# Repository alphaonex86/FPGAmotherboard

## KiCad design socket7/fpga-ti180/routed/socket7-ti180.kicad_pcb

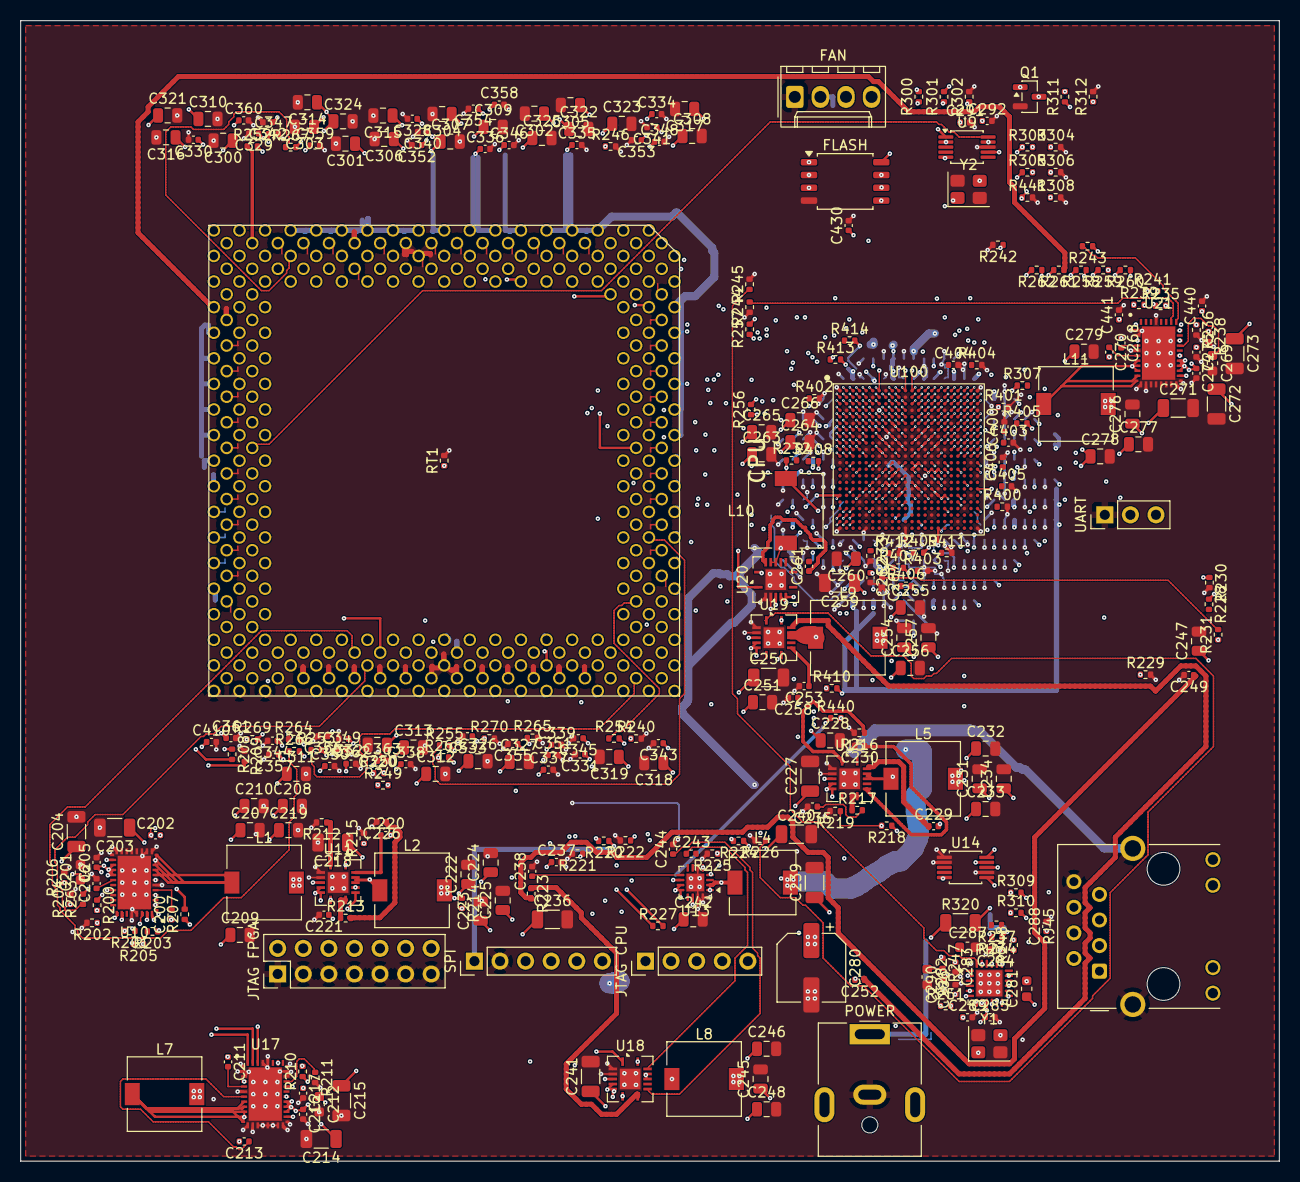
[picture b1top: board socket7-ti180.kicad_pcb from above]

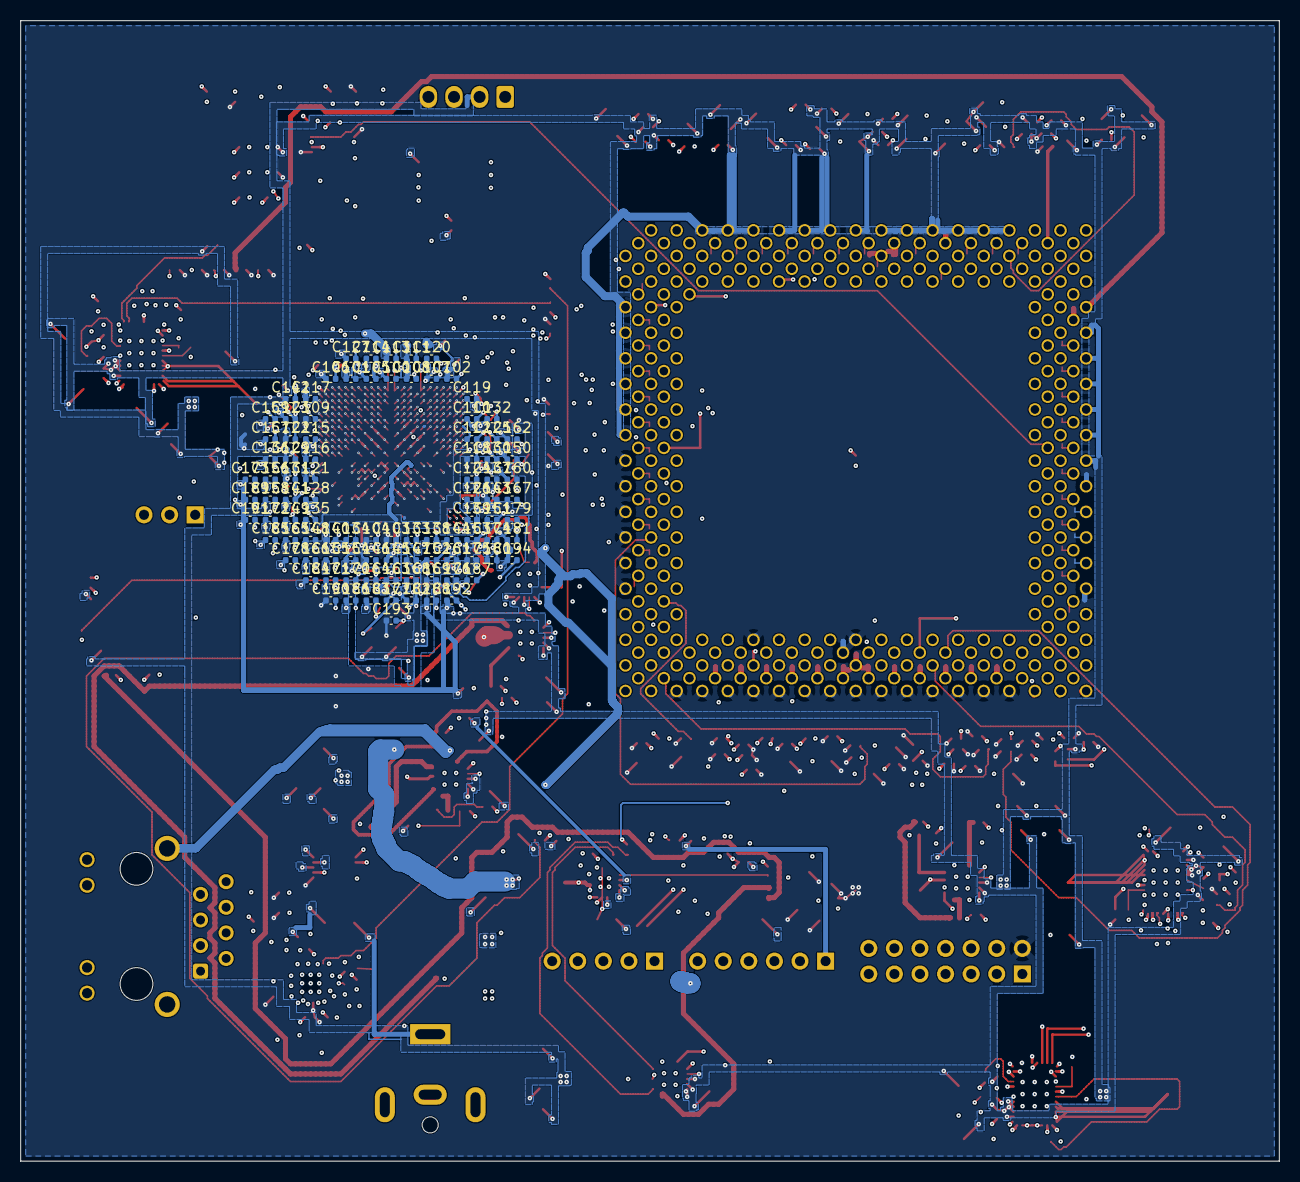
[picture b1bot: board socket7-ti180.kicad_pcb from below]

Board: 6 copper layers, 124.9 x 113.2 mm, 398 parts (95 on the bottom side), 290 nets.

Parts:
C100, C101, C102, C103, C104, C105, C106, C107, C108, C109, C110, C111, C112, C113, C114, C115, C116, C117, C118, C119, C120, C121, C122, C123, C124, C125, C126, C127, C128, C129, C130, C131, C132, C133, C134, C135, C136, C137, C138, C139, C140, C141, C142, C143, C144, C145, C146, C147, C148, C149, C150, C151, C152, C153, C154, C155, C156, C157, C158, C159, C160, C161, C162, C163, C164, C165, C166, C167, C168, C169, C170, C171, C172, C173, C174, C175, C176, C177, C178, C179, C180, C181, C182, C183, C184, C185, C186, C187, C188, C189, C190, C191, C192, C193, C194: 470nF; C_0402_1005Metric
C200, C211, C268: 1uF 16V X6S; C_0402_1005Metric
C201, C212, C269: 4.7uF 16V X5R; C_0603_1608Metric
C202, C213, C270: 100nF 16V X5R; C_0402_1005Metric
C203, C204, C214, C215, C218, C227, C236, C239, C240, C241, C250, C259, C271, C272, C273: 22uF 25V X5R; C_1206_3216Metric
C205, C216, C221, C230, C244, C253, C262, C274, C403, C404, C405, C406: 10nF 50V X7R; C_0402_1005Metric
C206, C217, C275: 1uF 25V X5R; C_0402_1005Metric
C207, C208, C209, C210, C222, C223, C224, C225, C245, C246, C247, C248, C254, C255, C256, C257, C263, C264, C265, C266, C276, C277, C278, C279: 47uF 6.3V X5R; C_0805_2012Metric
C219, C228, C242, C251, C260: 4.7uF 25V X7R; C_0805_2012Metric
C220, C229, C237, C243, C252, C261, C283, C284, C285, C288, C410, C430: 100nF 16V X7R; C_0402_1005Metric
C226, C235, C249, C258, C267: 8.2nF 50V X7R; C_0402_1005Metric
C231, C232, C233, C234: 47uF 10V X5R; C_0805_2012Metric
C238: 3.3nF 50V X7R; C_0402_1005Metric
C280: 100uF 25V; CP_Elec_6.3x7.7
C281: 600R@100MHz bead; L_0603_1608Metric
C282: 10uF 10V X5R; C_0603_1608Metric
C286: 470pF 50V C0G; C_0402_1005Metric
C287: 1uF 16V X7R; C_0603_1608Metric
C289, C290: 15pF 50V C0G; C_0402_1005Metric
C291, C292: 4pF 50V C0G; C_0402_1005Metric
C300, C301, C302, C303, C304, C305, C306, C307, C308, C309, C310, C311, C312, C313, C314, C315, C316, C317, C318, C319, C320, C321, C322, C323, C324, C325, C326, C327: 22uF; C_0805_2012Metric
C328, C329, C330, C331, C332, C333, C334, C335, C336, C337, C338, C339, C340, C341, C342, C343, C344, C345, C346, C347, C348, C349, C350, C351, C352, C353, C354, C355, C356, C357, C358, C359, C360, C361, C362, C363: 100nF; C_0402_1005Metric
C400: 1nF 50V C0G; C_0402_1005Metric
C440: 22nF 50V X7R; C_0402_1005Metric
C441: 1uF 16V X7R; C_0402_1005Metric
J1: HR911105A; RJ45_Hanrun_HR911105A_Horizontal
J2: SPI ISP; PinHeader_1x06_P2.54mm_Vertical
J3: PJ-063AH 12V; BarrelJack_CUI_PJ-063AH_Horizontal
J4: UART; PinHeader_1x03_P2.54mm_Vertical
J5: FPGA JTAG; PinHeader_2x07_P2.54mm_Vertical
J6: CPU JTAG; PinHeader_1x05_P2.54mm_Vertical
J7: fan 4-pin 1GND 2+12V 3TACH 4PWM; Molex_KK-254_AE-6410-04A_1x04_P2.54mm_Vertical
L1: VCC2 out; L_7.3x7.3_H4.5
L2: 3V3 out; L_7.3x7.3_H4.5
L4: 1V8 out; L_6.3x6.3_H3
L5: 5V out; L_7.3x7.3_H4.5
L7: VCC2 ph2 out; L_7.3x7.3_H4.5
L8: 0V95 out; L_7.3x7.3_H4.5
L9: 0V85 out; L_7.3x7.3_H4.5
L10: 1V1 out; L_7.3x7.3_H4.5
L11: 0V6 out; L_7.3x7.3_H4.5
Q1: BSS138; SOT-23
R200, R210, R234: 10R 1%; R_0402_1005Metric
R201, R202, R205, R239, R240: 21.5k 1%; R_0402_1005Metric
R203: 110k 1%; R_0402_1005Metric
R204: 56.2k 1%; R_0402_1005Metric
R206, R214, R235: 31.6k 1%; R_0402_1005Metric
R207, R215, R219, R221, R225, R229, R233, R246, R265, R270, R301, R302, R303, R305, R309, R310, R311, R400, R401, R402, R403, R404, R406, R407, R408, R409, R410, R411, R412, R413, R414, R440: 10k 1%; R_0402_1005Metric
R208, R209, R243, R244: 0R; R_0402_1005Metric
R211: 17.8k 1%; R_0402_1005Metric
R212, R216, R222, R226, R230: 100k 1%; R_0402_1005Metric
R213, R217, R223, R227, R231, R300: 1.69k 1%; R_0402_1005Metric
R218: 52.3k 1%; R_0402_1005Metric
R220: 12.4k 1%; R_0402_1005Metric
R224: 1.87k 1%; R_0402_1005Metric
R228: 619R 1%; R_0402_1005Metric
R232: 3.74k 1%; R_0402_1005Metric
R236: 6.81k 1%; R_0402_1005Metric
R237: 90.9k 1%; R_0402_1005Metric
R238: 46.4k 1%; R_0402_1005Metric
R241: 1.54k 1%; R_0402_1005Metric
R242: 5.62k 1%; R_0402_1005Metric
R245: 12.1k 1%; R_0402_1005Metric
R247, R248, R249, R250: 49.9 1%; R_0402_1005Metric
R251: 500R 1%; R_0402_1005Metric
R252, R261, R262, R264, R269: 8.2k 1%; R_0402_1005Metric
R253, R254, R255, R256, R257, R258, R259, R260, R263, R266, R267, R268: 4.7k 1%; R_0402_1005Metric
R304, R306, R312: 4.02k 1%; R_0402_1005Metric
R307: 30.9k 1%; R_0402_1005Metric
R308: 2.49k 1%; R_0402_1005Metric
R320: 10mR 1% 1W; R_1206_3216Metric
R405: 240R 1%; R_0402_1005Metric
R441: 22k 1%; R_0402_1005Metric
RT1: 10k NTC 1% B3380; R_0402_1005Metric
U7: LAN8720A-CP-TR; QFN-24-1EP_4x4mm_P0.5mm_EP2.6x2.6mm
U8: W25Q128JWSIQ; SOIC-8_5.3x5.3mm_P1.27mm
U9: SI5351A-B-GTR; MSOP-10_3x3mm_P0.5mm
U10: TPS546B24ARVFR VCC2; Texas_RVF0040A_LQFN-CLIP-40_5x7mm_P0.5mm
U11: TPS54620RGYR 3V3; Texas_S-PVQFN-N14
U13: TPS62130RGTR 1V8; QFN-16-1EP_3x3mm_P0.5mm_EP1.75x1.75mm
U14: INA226AIDGSR; MSOP-10_3x3mm_P0.5mm
U15: TPS54620RGYR 5V; Texas_S-PVQFN-N14
U17: TPS546B24ARVFR VCC2 ph2; Texas_RVF0040A_LQFN-CLIP-40_5x7mm_P0.5mm
U18: TPS54620RGYR 0V95; Texas_S-PVQFN-N14
U19: TPS54620RGYR 0V85; Texas_S-PVQFN-N14
U20: TPS54620RGYR 1V1; Texas_S-PVQFN-N14
U21: TPS546B24ARVFR 0V6; Texas_RVF0040A_LQFN-CLIP-40_5x7mm_P0.5mm
U100: Ti180J484D1C4
XU1: Socket 7 ZIF 321p; Socket7_P55C_296
Y1, Y2: 25MHz; Crystal_SMD_3225-4Pin_3.2x2.5mm

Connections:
0v62_gsense: R244.2, U21.34
0v62_sense: R243.2, U21.33
+0V62: C153.1, C155.1, C156.1, C157.1, C161.1, C163.1, C164.1, C168.1, C172.1, C178.1, C184.1, C185.1, C186.1, C276.1, C277.1, C278.1, C279.1, L11.2, R243.1, R405.2, U100.N8, U100.N10, U100.N14, U100.N15, U100.N16, U100.P9, U100.P11, U100.P13, U100.R16, U100.T15, U100.U14, U100.U16, U100.U17
+0V85: C139.1, C140.1, C141.1, C145.1, C146.1, C147.1, C148.1, C152.1, C154.1, C162.1, C166.1, C254.1, C255.1, C256.1, C257.1, L9.2, R228.1, U100.L10, U100.L12, U100.L14, U100.M9, U100.M11, U100.M12, U100.M13, U100.M15, U100.N9, U100.N12, U100.P16
+0V95: C114.1, C115.1, C116.1, C119.1, C120.1, C121.1, C122.1, C124.1, C125.1, C126.1, C127.1, C128.1, C129.1, C132.1, C133.1, C134.1, C135.1, C137.1, C138.1, C142.1, C144.1, C151.1, C158.1, C180.1, C245.1, C246.1, C247.1, C248.1, L8.2, R224.1, U100.G8, U100.G12, U100.G14, U100.G17, U100.H7, U100.H9, U100.H11, U100.H13, U100.H15, U100.J8, U100.J10, U100.J12, U100.J14, U100.J16, U100.K7, U100.K9, U100.K11, U100.K13, U100.K15, U100.L8, U100.L16, U100.M7, U100.N17, U100.T7
+1V1: C165.1, C167.1, C169.1, C170.1, C171.1, C174.1, C175.1, C176.1, C177.1, C182.1, C263.1, C264.1, C265.1, C266.1, L10.2, R232.1, U100.P7, U100.P15, U100.R8, U100.R9, U100.R10, U100.R12, U100.R14, U100.T11, U100.T13, U100.U10
+1V8: C100.1, C101.1, C102.1, C105.1, C106.1, C107.1, C108.1, C110.1, C111.1, C112.1, C113.1, C117.1, C123.1, C130.1, C131.1, C136.1, C143.1, C149.1, C150.1, C159.1, C160.1, C173.1, C179.1, C181.1, C183.1, C188.1, C189.1, C191.1, C192.1, C194.1, C239.1, C240.1, C430.1, J2.1, L4.2, R220.1, R406.2, R407.2, R408.2, R409.2, R410.2, R413.2, R414.2, U8.8, U13.14, U100.A3, U100.A13, U100.A19, U100.C4, U100.C9, U100.C14, U100.C19, U100.E5, U100.F9, U100.G1, U100.G10, U100.G21, U100.H17, U100.J2, U100.J22, U100.K20, U100.L3, U100.M6, U100.M17, U100.N4, U100.N19, U100.R20, U100.T3, U100.U1, U100.U7, U100.U12, U100.V19, U100.W6, U100.W22, U100.Y2
+3V3: C103.1, C104.1, C109.1, C118.1, C190.1, C193.1, C222.1, C223.1, C224.1, C225.1, C281.1, C285.1, C311.1, C312.1, C313.1, C318.1, C319.1, C320.1, C326.1, C327.1, C331.1, C332.1, C333.1, C337.1, C338.1, C339.1, C343.1, C344.1, C345.1, C349.1, C350.1, C351.1, C355.1, C356.1, C357.1, C361.1, C362.1, C363.1, C410.1, J5.2, L2.2, R207.1, R214.1, R252.2, R253.2, R254.2, R255.2, R256.2, R257.2, R258.2, R259.2, R260.2, R261.2, R262.2, R263.2, R264.2, R266.2, R267.2, R268.2, R269.2, R301.2, R305.1, R309.2, R310.2, R311.1, U7.9, U9.1, U9.7, U14.6, U100.AA13, U100.AB16, U100.E20, U100.G7, U100.W17, U100.Y10, XU1.A19 (VCC3), XU1.A21 (VCC3), XU1.A23 (VCC3), XU1.A25 (VCC3), XU1.A27 (VCC3), XU1.A29 (VCC3), XU1.AA37 (VCC3), XU1.AC37 (VCC3), XU1.AE37 (VCC3), XU1.AG37 (VCC3), XU1.AN21 (VCC3), XU1.AN23 (VCC3), XU1.AN25 (VCC3), XU1.AN27 (VCC3), XU1.AN29 (VCC3), XU1.E37 (VCC3), XU1.G37 (VCC3), XU1.J37 (VCC3), XU1.L33 (VCC3), XU1.L37 (VCC3), XU1.N37 (VCC3), XU1.Q37 (VCC3), XU1.S37 (VCC3), XU1.T34 (VCC3), XU1.U33 (VCC3), XU1.U37 (VCC3), XU1.W37 (VCC3), XU1.Y37 (VCC3)
+5V: C231.1, C232.1, C233.1, C234.1, C236.1, C237.1, L5.2, R218.1, R440.1, U13.10, U13.11, U13.12
+12V: C203.1, C204.1, C205.1, C214.1, C215.1, C216.1, C218.1, C219.1, C227.1, C228.1, C241.1, C242.1, C250.1, C251.1, C259.1, C260.1, C271.1, C272.1, C273.1, C274.1, C280.1, J7.2, R200.1, R210.1, R234.1, R307.1, R320.2, U10.22, U10.23, U10.24, U10.25, U11.4, U11.5, U11.6, U14.8, U14.9, U15.4, U15.5, U15.6, U17.22, U17.23, U17.24, U17.25, U18.4, U18.5, U18.6, U19.4, U19.5, U19.6, U20.4, U20.5, U20.6, U21.22, U21.23, U21.24, U21.25
+12V_IN: J3.1, R320.1, U14.10
GND: C100.2, C101.2, C102.2, C103.2, C104.2, C105.2, C106.2, C107.2, C108.2, C109.2, C110.2, C111.2, C112.2, C113.2, C114.2, C115.2, C116.2, C117.2, C118.2, C119.2, C120.2, C121.2, C122.2, C123.2, C124.2, C125.2, C126.2, C127.2, C128.2, C129.2, C130.2, C131.2, C132.2, C133.2, C134.2, C135.2, C136.2, C137.2, C138.2, C139.2, C140.2, C141.2, C142.2, C143.2, C144.2, C145.2, C146.2, C147.2, C148.2, C149.2, C150.2, C151.2, C152.2, C153.2, C154.2, C155.2, C156.2, C157.2, C158.2, C159.2, C160.2, C161.2, C162.2, C163.2, C164.2, C165.2, C166.2, C167.2, C168.2, C169.2, C170.2, C171.2, C172.2, C173.2, C174.2, C175.2, C176.2, C177.2, C178.2, C179.2, C180.2, C181.2, C182.2, C183.2, C184.2, C185.2, C186.2, C187.1, C187.2, C188.2, C189.2, C190.2, C191.2, C192.2, C193.2, C194.2, C201.2, C203.2, C204.2, C205.2, C206.2, C207.2, C208.2, C209.2, C210.2, C212.2, C214.2, C215.2, C216.2, C217.2, C218.2, C219.2, C221.2, C222.2, C223.2, C224.2, C225.2, C226.2, C227.2, C228.2, C230.2, C231.2, C232.2, C233.2, C234.2, C235.2, C236.2, C237.2, C238.2, C239.2, C240.2, C241.2, C242.2, C244.2, C245.2, C246.2, C247.2, C248.2, C249.2, C250.2, C251.2, C253.2, C254.2, C255.2, C256.2, C257.2, C258.2, C259.2, C260.2, C262.2, C263.2, C264.2, C265.2, C266.2, C267.2, C269.2, C271.2, C272.2, C273.2, C274.2, C275.2, C276.2, C277.2, C278.2, C279.2, C280.2, C282.2, C283.2, C284.2, C285.2, C286.2, C287.2, C288.2, C289.2, C290.2, C291.2, C292.2, C300.2, C301.2, C302.2, C303.2, C304.2, C305.2, C306.2, C307.2, C308.2, C309.2, C310.2, C311.2, C312.2, C313.2, C314.2, C315.2, C316.2, C317.2, C318.2, C319.2, C320.2, C321.2, C322.2, C323.2, C324.2, C325.2, C326.2, C327.2, C328.2, C329.2, C330.2, C331.2, C332.2, C333.2, C334.2, C335.2, C336.2, C337.2, C338.2, C339.2, C340.2, C341.2, C342.2, C343.2, C344.2, C345.2, C346.2, C347.2, C348.2, C349.2, C350.2, C351.2, C352.2, C353.2, C354.2, C355.2, C356.2, C357.2, C358.2, C359.2, C360.2, C361.2, C362.2, C363.2, C400.2, C403.2, C404.2, C405.2, C406.2, C410.2, C430.2, C440.2, C441.2, J1.8, J1.SH, J2.2, J3.2, J4.1, J5.1, J5.3, J5.5, J5.7, J5.9, J5.11, J5.13, J7.1, Q1.2, R202.2, R204.2, R206.2, R209.1, R211.2, R212.2, R215.2, R216.2, R219.2, R221.2, R222.2, R225.2, R226.2, R229.2, R230.2, R233.2, R236.2, R238.2, R240.2, R242.2, R244.1, R245.2, R246.2, R265.2, R270.2, R302.2, R304.2, R306.2, R308.2, R312.2, R400.2, R401.2, R402.2, R403.2, R404.2, R411.2, R412.2, R441.2, RT1.2, U7.25, U8.4, U9.8, U10.6, U10.13, U10.14, U10.15, U10.16, U10.17, U10.18, U10.19, U10.20, U10.21, U10.36, U10.37, U10.41, U11.2, U11.3, U11.15, U13.6, U13.15, U13.16, U13.17, U14.1, U14.2, U14.7, U15.2, U15.3, U15.15, U17.1, U17.2, U17.3, U17.6, U17.13, U17.14, U17.15, U17.16, U17.17, U17.18, U17.19, U17.20, U17.21, U17.30, U17.31, U17.32, U17.36, U17.37, U17.41, U18.2, U18.3, U18.15, U19.2, U19.3, U19.15, U20.2, U20.3, U20.15, U21.2, U21.3, U21.6, U21.13, U21.14, U21.15, U21.16, U21.17, U21.18, U21.19, U21.20, U21.21, U21.37, U21.41, U100.A1, U100.A8, U100.A22, U100.AA8, U100.AA19, U100.AB1, U100.AB5, U100.AB11, U100.AB22, U100.B6, U100.B11, U100.B16, U100.D2, U100.D7, U100.D12, U100.D17, U100.D22, U100.E15, U100.F3, U100.F18, U100.G9, U100.G11, U100.G13, U100.G15, U100.H4, U100.H8, U100.H10, U100.H12, U100.H14, U100.H16, U100.H19, U100.J7, U100.J9, U100.J11, U100.J13, U100.J15, U100.K5, U100.K8, U100.K10, U100.K12, U100.K14, U100.K16, U100.K17, U100.L7, U100.L9, U100.L11, U100.L13, U100.L15, U100.M1, U100.M8, U100.M10, U100.M14, U100.M16, U100.M21, U100.N7, U100.N11, U100.N13, U100.P2, U100.P8, U100.P10, U100.P12, U100.P14, U100.P22, U100.R7, U100.R11, U100.R13, U100.R15, U100.R17, U100.T8, U100.T10, U100.T12, U100.T14, U100.T16, U100.U5, U100.U13, U100.U15, U100.U21, U100.V4, U100.V9, U100.W7, U100.W20, U100.Y5, U100.Y15, XU1.AB02 (VSS), XU1.AB04 (HOLD), XU1.AB36 (VSS), XU1.AD02 (VSS), XU1.AD36 (VSS), XU1.AF02 (VSS), XU1.AF36 (VSS), XU1.AH02 (VSS), XU1.AJ37 (VSS), XU1.AL37 (VSS), XU1.AM08 (VSS), XU1.AM10 (VSS), XU1.AM12 (VSS), XU1.AM14 (VSS), XU1.AM16 (VSS), XU1.AM18 (VSS), XU1.AM20 (VSS), XU1.AM22 (VSS), XU1.AM24 (VSS), XU1.AM26 (VSS), XU1.AM28 (VSS), XU1.AM30 (VSS), XU1.AN37 (VSS), XU1.B06 (VSS), XU1.B08 (VSS), XU1.B10 (VSS), XU1.B12 (VSS), XU1.B14 (VSS), XU1.B16 (VSS), XU1.B18 (VSS), XU1.B20 (VSS), XU1.B22 (VSS), XU1.B24 (VSS), XU1.B26 (VSS), XU1.B28 (VSS), XU1.H02 (VSS), XU1.H36 (VSS), XU1.K02 (VSS), XU1.K36 (VSS), XU1.M02 (VSS), XU1.M36 (VSS), XU1.P02 (VSS), XU1.P36 (VSS), XU1.R02 (VSS), XU1.R36 (VSS), XU1.T02 (VSS), XU1.T36 (VSS), XU1.U35 (VSS), XU1.V02 (VSS), XU1.V36 (VSS), XU1.W03 (EWBE#), XU1.X02 (VSS), XU1.X36 (VSS), XU1.Z02 (VSS), XU1.Z36 (VSS), Y1.2, Y1.4, Y2.2, Y2.4
VCC2: C207.1, C208.1, C209.1, C210.1, C300.1, C301.1, C302.1, C303.1, C304.1, C305.1, C306.1, C307.1, C308.1, C309.1, C310.1, C314.1, C315.1, C316.1, C317.1, C321.1, C322.1, C323.1, C324.1, C325.1, C328.1, C329.1, C330.1, C334.1, C335.1, C336.1, C340.1, C341.1, C342.1, C346.1, C347.1, C348.1, C352.1, C353.1, C354.1, C358.1, C359.1, C360.1, L1.2, L7.2, R208.1, R303.1, XU1.A07 (VCC2), XU1.A09 (VCC2), XU1.A11 (VCC2), XU1.A13 (VCC2), XU1.A15 (VCC2), XU1.A17 (VCC2), XU1.AA01 (VCC2), XU1.AC01 (VCC2), XU1.AE01 (VCC2), XU1.AG01 (VCC2), XU1.AN09 (VCC2), XU1.AN11 (VCC2), XU1.AN13 (VCC2), XU1.AN15 (VCC2), XU1.AN17 (VCC2), XU1.AN19 (VCC2), XU1.G01 (VCC2), XU1.J01 (VCC2), XU1.L01 (VCC2), XU1.N01 (VCC2), XU1.Q01 (VCC2), XU1.S01 (VCC2), XU1.U01 (VCC2), XU1.W01 (VCC2), XU1.Y01 (VCC2)
cbsel0: R411.1, U100.R6
cbsel1: R412.1, U100.T6
cck: J2.4, U8.6, U100.AA3
cdi0: J2.6, U8.5, U100.W2
cdi1: J2.5, U8.2, U100.W3
cdi2: R413.1, U8.3, U100.AA1
cdi3: R414.1, U8.7, U100.Y1
cdone: R407.1, U100.U8
cpu_a20m_n: U100.E3, XU1.AK08 (A20M#)
cpu_a[3]: U100.J4, XU1.AL35 (A3)
cpu_a[4]: U100.H5, XU1.AM34 (A4)
cpu_a[5]: U100.K1, XU1.AK32 (A5)
cpu_a[6]: U100.C18, XU1.AN33 (A6)
cpu_a[7]: U100.J3, XU1.AL33 (A7)
cpu_a[8]: U100.B15, XU1.AM32 (A8)
cpu_a[9]: U100.E9, XU1.AK30 (A9)
cpu_a[10]: U100.J1, XU1.AN31 (A10)
cpu_a[11]: U100.G4, XU1.AL31 (A11)
cpu_a[12]: U100.G6, XU1.AL29 (A12)
cpu_a[13]: U100.E11, XU1.AK28 (A13)
cpu_a[14]: U100.E7, XU1.AL27 (A14)
cpu_a[15]: U100.H1, XU1.AK26 (A15)
cpu_a[16]: U100.D13, XU1.AL25 (A16)
cpu_a[17]: U100.G3, XU1.AK24 (A17)
cpu_a[18]: U100.F6, XU1.AL23 (A18)
cpu_a[19]: U100.F7, XU1.AK22 (A19)
cpu_a[20]: U100.F1, XU1.AL21 (A20)
cpu_a[21]: U100.D19, XU1.AF34 (A21)
cpu_a[22]: U100.D16, XU1.AH36 (A22)
cpu_a[23]: U100.J5, XU1.AE33 (A23)
cpu_a[24]: U100.F10, XU1.AG35 (A24)
cpu_a[25]: U100.K3, XU1.AJ35 (A25)
cpu_a[26]: U100.F11, XU1.AH34 (A26)
cpu_a[27]: U100.F13, XU1.AG33 (A27)
cpu_a[28]: U100.D15, XU1.AK36 (A28)
cpu_a[29]: U100.K2, XU1.AK34 (A29)
cpu_a[30]: U100.L1, XU1.AM36 (A30)
cpu_a[31]: U100.F12, XU1.AJ33 (A31)
cpu_ads_n: U100.E2, XU1.AJ05 (ADS#)
cpu_ahold: U100.C5, XU1.V04 (AHOLD)
cpu_ap: R252.1, XU1.AK02 (AP)
cpu_be[0]: U100.C3, XU1.AL09 (BE0#)
cpu_be[1]: U100.D3, XU1.AK10 (BE1#)
cpu_be[2]: U100.E8, XU1.AL11 (BE2#)
cpu_be[3]: U100.D5, XU1.AK12 (BE3#)
cpu_be[4]: U100.F4, XU1.AL13 (BE4#)
cpu_be[5]: U100.D11, XU1.AK14 (BE5#)
cpu_be[6]: U100.F2, XU1.AL15 (BE6#)
cpu_be[7]: U100.D10, XU1.AK16 (BE7#)
cpu_bf[0]: U100.G2, XU1.Y33 ([BF0])
cpu_bf[1]: U100.C16, XU1.X34 ([BF1])
cpu_boff_n: U100.B2, XU1.Z04 (BOFF#)
cpu_brdy_n: U100.B9, XU1.X04 (BRDY#)
cpu_cache_n: U100.B5, XU1.U03 (CACHE#)
cpu_clk: U9.10, XU1.AK18 (CLK)
cpu_d[0]: U100.C17, XU1.K34 (D0)
cpu_d[1]: U100.K18, XU1.G35 (D1)
cpu_d[2]: U100.D18, XU1.J35 (D2)
cpu_d[3]: U100.C20, XU1.G33 (D3)
cpu_d[4]: U100.L19, XU1.F36 (D4)
cpu_d[5]: U100.J19, XU1.F34 (D5)
cpu_d[6]: U100.H18, XU1.E35 (D6)
cpu_d[7]: U100.C21, XU1.E33 (D7)
cpu_d[8]: U100.K19, XU1.D34 (D8)
cpu_d[9]: U100.N22, XU1.C37 (D9)
cpu_d[10]: U100.K21, XU1.C35 (D10)
cpu_d[11]: U100.J18, XU1.B36 (D11)
cpu_d[12]: U100.E18, XU1.D32 (D12)
cpu_d[13]: U100.T22, XU1.B34 (D13)
cpu_d[14]: U100.H20, XU1.C33 (D14)
cpu_d[15]: U100.L20, XU1.A35 (D15)
cpu_d[16]: U100.G19, XU1.B32 (D16)
cpu_d[17]: U100.F14, XU1.C31 (D17)
cpu_d[18]: U100.G18, XU1.A33 (D18)
cpu_d[19]: U100.G16, XU1.D28 (D19)
cpu_d[20]: U100.F17, XU1.B30 (D20)
cpu_d[21]: U100.B17, XU1.C29 (D21)
cpu_d[22]: U100.F19, XU1.A31 (D22)
cpu_d[23]: U100.B18, XU1.D26 (D23)
cpu_d[24]: U100.E16, XU1.C27 (D24)
cpu_d[25]: U100.L5, XU1.C23 (D25)
cpu_d[26]: U100.E13, XU1.D24 (D26)
cpu_d[27]: U100.E14, XU1.C21 (D27)
cpu_d[28]: U100.B21, XU1.D22 (D28)
cpu_d[29]: U100.L2, XU1.C19 (D29)
cpu_d[30]: U100.D8, XU1.D20 (D30)
cpu_d[31]: U100.D9, XU1.C17 (D31)
cpu_d[32]: U100.H3, XU1.C15 (D32)
cpu_d[33]: U100.F8, XU1.D16 (D33)
cpu_d[34]: U100.E6, XU1.C13 (D34)
cpu_d[35]: U100.M3, XU1.D14 (D35)
cpu_d[36]: U100.H2, XU1.C11 (D36)
cpu_d[37]: U100.D14, XU1.D12 (D37)
cpu_d[38]: U100.C11, XU1.C09 (D38)
cpu_d[39]: U100.C10, XU1.D10 (D39)
cpu_d[40]: U100.D6, XU1.D08 (D40)
cpu_d[41]: U100.B10, XU1.A05 (D41)
cpu_d[42]: U100.F5, XU1.E09 (D42)
cpu_d[43]: U100.A18, XU1.B04 (D43)
cpu_d[44]: U100.C12, XU1.D06 (D44)
cpu_d[45]: U100.C7, XU1.C05 (D45)
cpu_d[46]: U100.D4, XU1.E07 (D46)
cpu_d[47]: U100.B19, XU1.C03 (D47)
cpu_d[48]: U100.B4, XU1.D04 (D48)
cpu_d[49]: U100.C6, XU1.E05 (D49)
cpu_d[50]: U100.A20, XU1.D02 (D50)
cpu_d[51]: U100.B13, XU1.F04 (D51)
cpu_d[52]: U100.A7, XU1.E03 (D52)
cpu_d[53]: U100.B7, XU1.G05 (D53)
cpu_d[54]: U100.A5, XU1.E01 (D54)
cpu_d[55]: U100.A14, XU1.G03 (D55)
cpu_d[56]: U100.B8, XU1.H04 (D56)
cpu_d[57]: U100.A12, XU1.J03 (D57)
cpu_d[58]: U100.B22, XU1.J05 (D58)
cpu_d[59]: U100.B12, XU1.K04 (D59)
cpu_d[60]: U100.C13, XU1.L05 (D60)
cpu_d[61]: U100.A17, XU1.L03 (D61)
cpu_d[62]: U100.A16, XU1.M04 (D62)
cpu_d[63]: U100.B14, XU1.N03 (D63)
cpu_dc_n: U100.C1, XU1.AK04 (D/C#)
cpu_dp[0]: R253.1, XU1.D36 (DP0)
cpu_dp[1]: R254.1, XU1.D30 (DP1)
cpu_dp[2]: R255.1, XU1.C25 (DP2)
cpu_dp[3]: R256.1, XU1.D18 (DP3)
cpu_dp[4]: R257.1, XU1.C07 (DP4)
cpu_dp[5]: R258.1, XU1.F06 (DP5)
cpu_dp[6]: R259.1, XU1.F02 (DP6)
cpu_dp[7]: R260.1, XU1.N05 (DP7)
cpu_eads_n: U100.E4, XU1.AM04 (EADS#)
cpu_flush_n: R261.1, XU1.AN07 (FLUSH#)
cpu_frcmc_n: R262.1, XU1.Y35 (FRCMC#1)
cpu_hitm_n: U100.D1, XU1.AL05 (HITM#)
cpu_ignne_n: R263.1, XU1.AA35 (IGNNE#)
cpu_init: U100.E10, XU1.AA33 (INIT)
cpu_intr: U100.C15, XU1.AD34 (INTR/LINT0)
cpu_ken_inv_n: U100.A4, XU1.U05 (INV), XU1.W05 (KEN#)
cpu_lock_n: U100.C2, XU1.AH04 (LOCK#)
cpu_mio_n: U100.A2, XU1.T04 (M/IO#)
cpu_na_n: U100.B3, XU1.Y05 (NA#)
cpu_nmi: U100.K4, XU1.AC33 (NMI/LINT1)
cpu_pen_n: R264.1, XU1.Z34 (PEN#)
cpu_picd1: R265.1, XU1.L35 (PICD1)
cpu_reset: R269.1, U100.A15, XU1.AK20 (RESET)
cpu_smi_n: R266.1, XU1.AB34 (SMI#)
cpu_smiact_n: R267.1, XU1.AG03 (SMIACT#)
cpu_stpclk_n: R268.1, XU1.V34 (STPCLK#)
cpu_tck: J6.1, XU1.M34 (TCK)
cpu_tdi: J6.3, XU1.N35 (TDI)
cpu_tdo: J6.4, XU1.N33 (TDO)
cpu_tms: J6.2, XU1.P34 (TMS)
cpu_trst_n: J6.5, R270.1, XU1.Q33 (TRST#)
cpu_wbwt_n: U100.B1, XU1.AA05 (WB/WT#)
cpu_wr_n: U100.E1, XU1.AM06 (W/R#)
creset_n: C441.1, R406.1, U11.14, U13.4, U20.14, U21.1, U100.T9
csi: R408.1, U100.AA2
en_grp2: C440.1, R440.2, R441.1, U11.10, U13.13, U18.14, U19.14, U20.10, U21.27
en_vcc2: U10.27, U17.27, U100.A6
eth_mdc: U7.13, U100.F21
eth_mdi_rxn: J1.6, R250.1, U7.22
eth_mdi_rxp: J1.3, R249.1, U7.23
eth_mdi_txn: J1.2, R248.1, U7.20
eth_mdi_txp: J1.1, R247.1, U7.21
eth_mdio: U7.12, U100.F20
eth_nintsel: R246.1, U7.2
eth_rbias: R245.1, U7.24
eth_ref_clk: U7.14, U100.F22
eth_rmii_crs_dv: U7.11, U100.G22
eth_rmii_rx_er: U7.10, U100.H22
eth_rmii_rxd[0]: U7.8, U100.H21
eth_rmii_rxd[1]: U7.7, U100.J21
eth_rmii_tx_en: U7.16, U100.E22
eth_rmii_txd[0]: U7.17, U100.D20
eth_rmii_txd[1]: U7.18, U100.D21
eth_rst_n: U7.15, U100.E21
eth_vdda: C281.2, C282.1, C283.1, C284.1, C288.1, J1.4, J1.5, R247.2, R248.2, R249.2, R250.2, U7.1, U7.19
eth_vddcr: C286.1, C287.1, U7.6
eth_xtal1: C289.1, U7.5, Y1.1
eth_xtal2: C290.1, R251.1, Y1.3
eth_xtal2_drv: R251.2, U7.4
fan_pwm: J7.4, Q1.3
fan_pwm_g: Q1.1, R302.1, U100.M22
fan_tach: J7.3, R300.1, R301.1
fan_tach_f: C400.1, R300.2, U100.C22
fpga_refclk: U9.9, U100.A11
i2c_scl: R309.1, U9.4, U10.3, U14.5, U100.A10
i2c_sda: R310.1, U9.5, U10.2, U14.4, U100.A9
jtag_tck: J5.6, U100.F15
jtag_tdi: J5.10, U100.F16
jtag_tdo: J5.8, U100.E17
jtag_tms: J5.4, U100.B20
ref_res_2a: R400.1, U100.U19
ref_res_2c: R401.1, U100.J17
ref_res_3a: R404.1, U100.E19
ref_res_4a: R402.1, U100.G5
ref_res_4c: R403.1, U100.U4
ssl_n: J2.3, R410.1, U8.1, U100.Y3
sw_0v62: C270.2, L11.1, U21.8, U21.9, U21.10, U21.11, U21.12
sw_0v85: C252.2, L9.1, U19.11, U19.12
sw_0v95: C243.2, L8.1, U18.11, U18.12
sw_1v1: C261.2, L10.1, U20.11, U20.12
sw_1v8: L4.1, U13.1, U13.2, U13.3
sw_3v3: C220.2, L2.1, U11.11, U11.12
sw_5v: C229.2, L5.1, U15.11, U15.12
sw_vcc2: C202.2, L1.1, U10.8, U10.9, U10.10, U10.11, U10.12
sw_vcc2_b: C213.2, L7.1, U17.8, U17.9, U17.10, U17.11, U17.12
test_n: R409.1, U100.T5
tsen_socket: C406.1, R311.2, R312.1, RT1.1, U100.L21
u9_xa: C291.1, U9.2, Y2.1
u9_xb: C292.1, U9.3, Y2.3
u10_avin: C206.1, R200.2, U10.26
u10_boot: C202.1, U10.7
u10_bp1v5: C200.1, R201.1, R203.1, R205.1, U10.4
u10_drtn: C200.2, U10.5
u10_msel1: R201.2, R202.1, U10.32
u10_msel2: R203.2, R204.1, U10.29
u10_pgood: R207.2, U10.1
u10_vdd5: C201.1, U10.28
u10_vsel: R205.2, R206.1, U10.30
u11_boot: C220.1, U11.13
u11_comp: R213.1, U11.8
u11_compz: C226.1, R213.2
u11_fb: R214.2, R215.1, U11.7
u11_rt: R212.1, U11.1
u11_ss: C221.1, U11.9
u13_fb: R220.2, R221.1, U13.5
u13_ss: C238.1, U13.9
u15_boot: C229.1, U15.13
u15_comp: R217.1, U15.8
u15_compz: C235.1, R217.2
u15_fb: R218.2, R219.1, U15.7
u15_rt: R216.1, U15.1
u15_ss: C230.1, U15.9
u17_avin: C217.1, R210.2, U17.26
u17_boot: C213.1, U17.7
u17_bp1v5: C211.1, U17.4, U17.34
u17_drtn: C211.2, U17.5
u17_msel2: R211.1, U17.29
u17_vdd5: C212.1, U17.28
u18_boot: C243.1, U18.13
u18_comp: R223.1, U18.8
u18_compz: C249.1, R223.2
u18_fb: R224.2, R225.1, U18.7
u18_rt: R222.1, U18.1
u18_ss: C244.1, U18.9
u19_boot: C252.1, U19.13
u19_comp: R227.1, U19.8
u19_compz: C258.1, R227.2
u19_fb: R228.2, R229.1, U19.7
u19_rt: R226.1, U19.1
u19_ss: C253.1, U19.9
u20_boot: C261.1, U20.13
u20_comp: R231.1, U20.8
u20_compz: C267.1, R231.2
u20_fb: R232.2, R233.1, U20.7
u20_rt: R230.1, U20.1
u20_ss: C262.1, U20.9
u21_adrsel: R241.2, R242.1, U21.31
u21_avin: C275.1, R234.2, U21.26
u21_boot: C270.1, U21.7
u21_bp1v5: C268.1, R235.1, R237.1, R239.1, R241.1, U21.4
u21_drtn: C268.2, U21.5
u21_msel1: R239.2, R240.1, U21.32
u21_msel2: R237.2, R238.1, U21.29
u21_vdd5: C269.1, U21.28
u21_vsel: R235.2, R236.1, U21.30
uart_rx: J4.2, U100.G20
uart_tx: J4.3, U100.J20
vcc2_bcx_clk: U10.39, U17.39
vcc2_bcx_dat: U10.40, U17.40
vcc2_gsense: R209.2, U10.34
vcc2_sense: R208.2, U10.33
vcc2_sync: U10.38, U17.38
vcc2_vshare: U10.35, U17.35
vsen_3v3: C404.1, R305.2, R306.1, U100.A21
vsen_12v: C405.1, R307.2, R308.1, U100.L22
vsen_vcc2: C403.1, R303.2, R304.1, U100.K22
zq: R405.1, U100.V11
